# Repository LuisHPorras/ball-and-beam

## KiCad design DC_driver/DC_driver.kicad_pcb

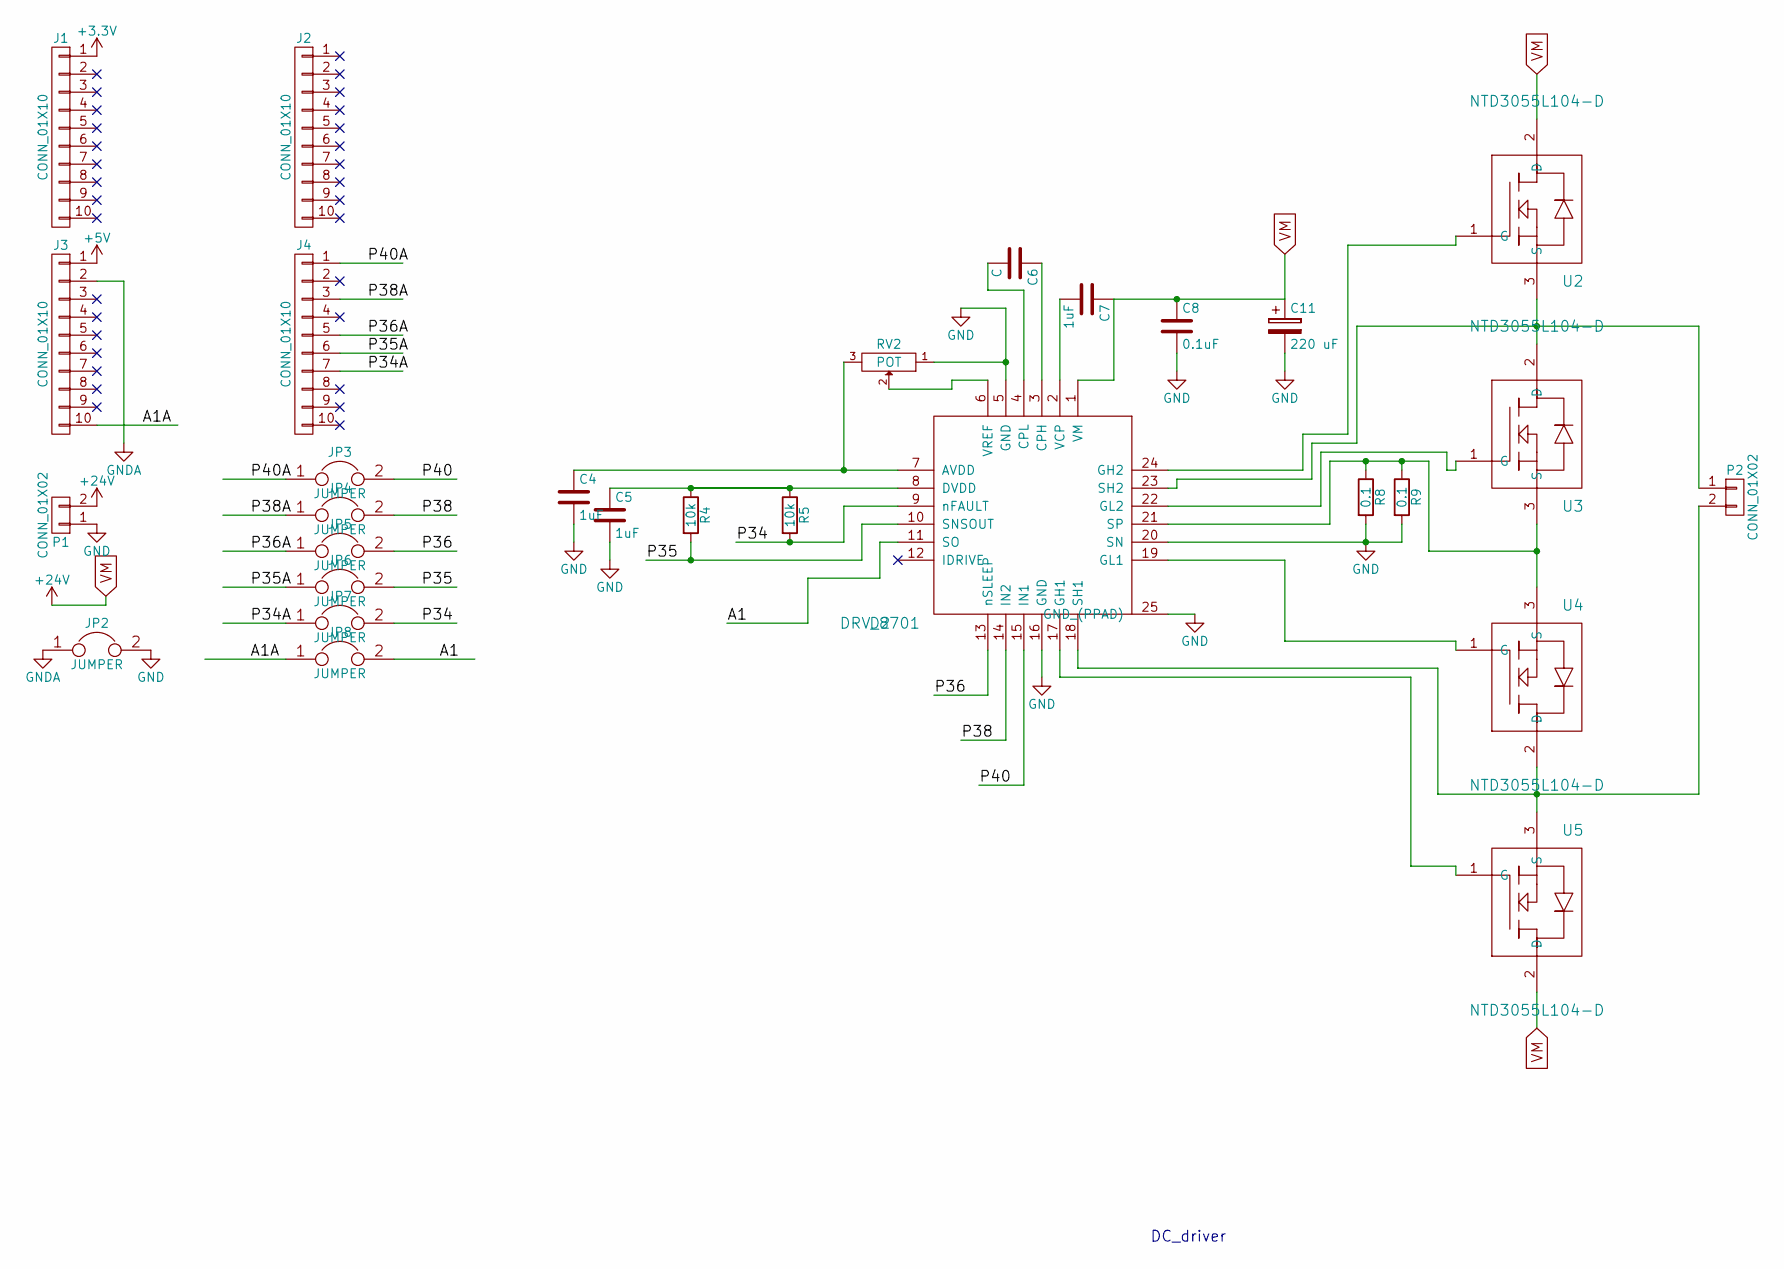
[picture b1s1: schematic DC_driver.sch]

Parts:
C4, C5, C7: 1uF; C_1206
C6: C; C_1206
C8: 0.1uF; C_1206
C11: 220 uF; C_Radial_D8_L11.5_P3.5
D2: DRV_8701; QFN-24-1EP_4x4mm_Pitch0.5mm
J1, J2, J3, J4: CONN_01X10; Pin_Header_Straight_1x10
JP2, JP3, JP4, JP5, JP6, JP7, JP8: JUMPER; Pin_Header_Straight_1x02
P1, P2: CONN_01X02; bornier2
R4, R5: 10k; R_1206
R8, R9: 0.1; R_1206
RV2: POT; POT_SMD
U2, U3, U4, U5: NTD3055L104-D; TO-252-2Lead

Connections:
+3V3: J1.1
+5V: J3.1
/A1: D2.11 (SO), JP8.2
/A1A: J3.10, JP8.1
/P34: D2.9 (nFAULT), JP7.2, R5.2
/P34A: J4.7, JP7.1
/P35: D2.10 (SNSOUT), JP6.2, R4.2
/P35A: J4.6, JP6.1
/P36: D2.13 (nSLEEP), JP5.2
/P36A: J4.5, JP5.1
/P38: D2.14 (IN2), JP4.2
/P38A: J4.3, JP4.1
/P40: D2.15 (IN1), JP3.2
/P40A: J4.1, JP3.1
GND: C4.2, C5.2, C8.2, C11.2, D2.5 (GND), D2.16 (GND), D2.20 (SN), D2.25 (GND_(PPAD)), JP2.2, P1.1, R8.2, R9.2, RV2.1
GNDA: J3.2, JP2.1
unnamed: C4.1, D2.7 (AVDD), RV2.3
unnamed: C5.1, D2.8 (DVDD), R4.1, R5.1
unnamed: C6.1, D2.3 (CPH)
unnamed: C6.2, D2.4 (CPL)
unnamed: C7.2, D2.2 (VCP)
unnamed: D2.6 (VREF), RV2.2
unnamed: D2.17 (GH1), U5.1 (G)
unnamed: D2.18 (SH1), P2.2, U4.2 (D), U5.3 (S)
unnamed: D2.19 (GL1), U4.1 (G)
unnamed: D2.21 (SP), R8.1, R9.1, U3.3 (S), U4.3 (S)
unnamed: D2.22 (GL2), U3.1 (G)
unnamed: D2.23 (SH2), P2.1, U2.3 (S), U3.2 (D)
unnamed: D2.24 (GH2), U2.1 (G)
VM: C7.1, C8.1, C11.1, D2.1 (VM), P1.2, U2.2 (D), U5.2 (D)

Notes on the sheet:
DC_driver

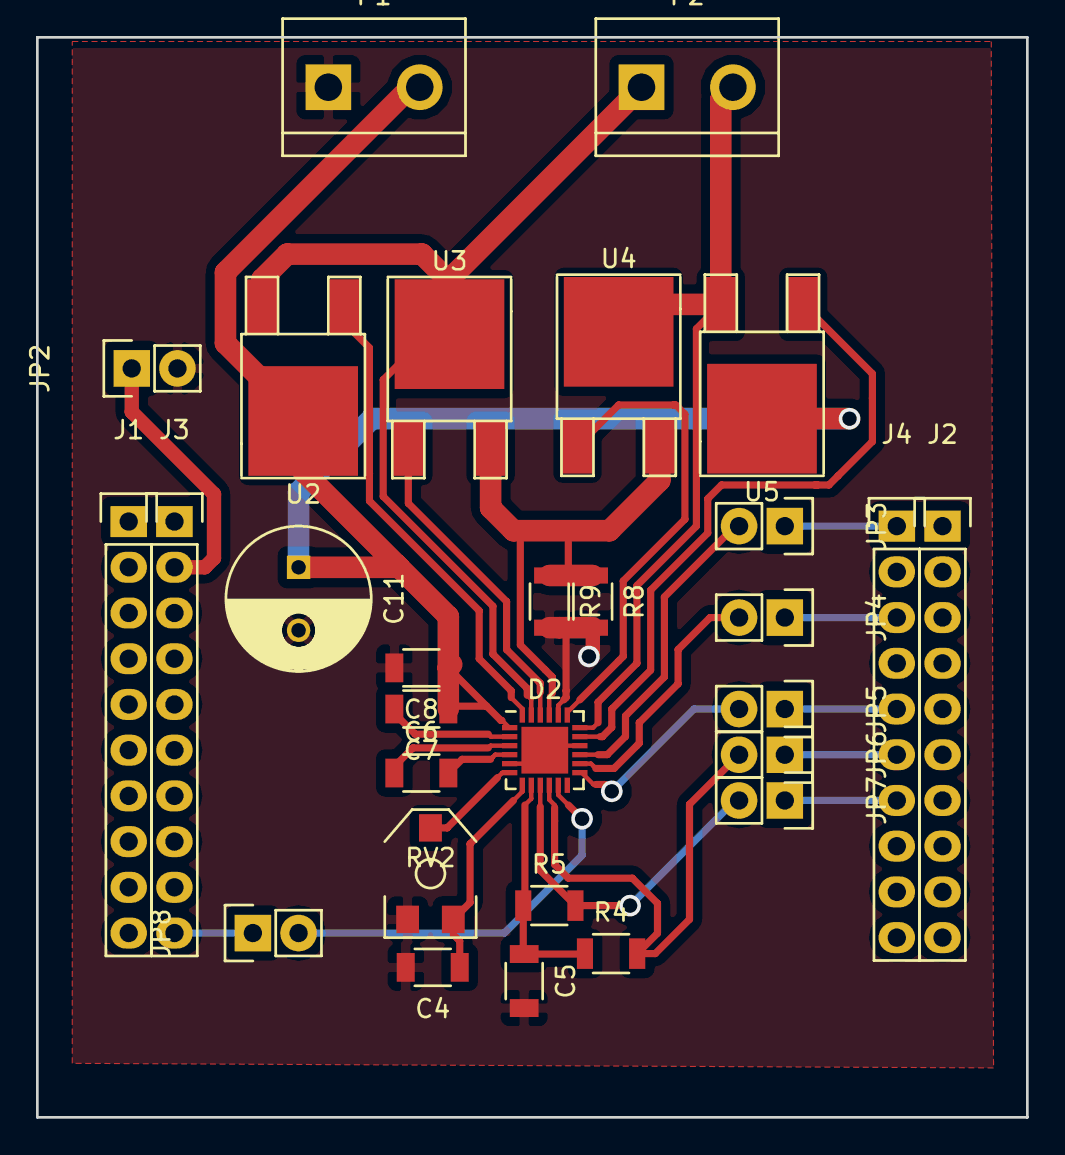
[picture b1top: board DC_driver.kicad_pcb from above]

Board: 2 copper layers, 55.0 x 60.0 mm, 29 parts (0 on the bottom side), 28 nets.

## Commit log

2016-02-21 dc driver and 3,3v step down
2016-02-21 Rename
2016-02-21 main changes
